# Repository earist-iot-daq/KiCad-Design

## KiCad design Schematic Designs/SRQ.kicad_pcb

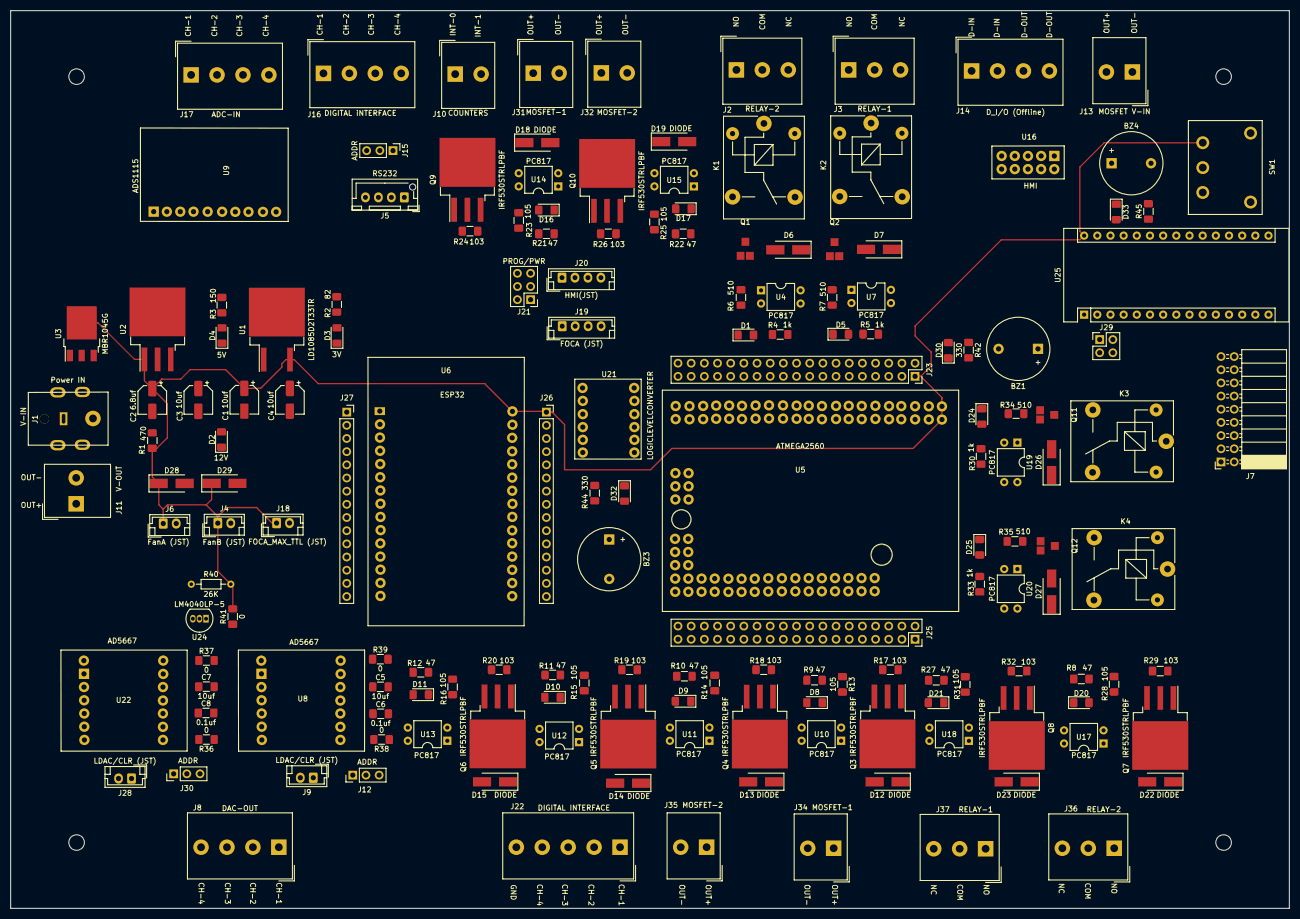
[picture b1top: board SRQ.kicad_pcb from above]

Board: 2 copper layers, 246.6 x 173.1 mm, 163 parts (0 on the bottom side), 240 nets.

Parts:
BZ1, BZ3, BZ4: Buzzer; Buzzer_12x9.5RM7.6
C1, C3, C4: 10uf; CP_Elec_5x5.4
C2: 6.8uf; CP_Elec_5x5.8
C5, C7: 10uf; C_1206_3216Metric_Pad1.42x1.75mm_HandSolder
C6, C8: 0.1uf; C_1206_3216Metric_Pad1.42x1.75mm_HandSolder
D1, D5, D8, D9, D10, D11, D16, D17, D20, D21, D24, D25: LED; LED_1206_3216Metric_Pad1.42x1.75mm_HandSolder
D2, D3, D4, D30, D32, D33: LED; D_1206_3216Metric_Pad1.42x1.75mm_HandSolder
D6, D7, D12, D13, D14, D15, D18, D19, D22, D23, D26, D27, D28, D29: DIODE; D_SMA_Handsoldering
J1: V-IN; DC Power Receptable Jack 8A 2mm Through hole
J2, J36: RELAY-2; Altech_AK300_1x03_P5.00mm_45-Degree
J3, J37: RELAY-1; Altech_AK300_1x03_P5.00mm_45-Degree
J4: FanB (JST); JST_EH_B2B-EH-A_1x02_P2.50mm_Vertical
J5: RS232; JST_XH_B4B-XH-AM_1x04_P2.50mm_Vertical
J6: FanA (JST); JST_EH_B2B-EH-A_1x02_P2.50mm_Vertical
J7: ARDUINO_NANO_pinheaders; PinSocket_2x09_P2.54mm_Horizontal
J8: DAC-OUT; Altech_AK300_1x04_P5.00mm_45-Degree
J9, J28: LDAC/CLR (JST); JST_EH_B2B-EH-A_1x02_P2.50mm_Vertical
J10: COUNTERS; Altech_AK300_1x02_P5.00mm_45-Degree
J11: V-OUT; Altech_AK300_1x02_P5.00mm_45-Degree
J12, J15, J30: ADDR; PinHeader_1x03_P2.54mm_Vertical
J13: MOSFET V-IN; Altech_AK300_1x02_P5.00mm_45-Degree
J14: D_I/O (Offline); Altech_AK300_1x04_P5.00mm_45-Degree
J16: DIGITAL iNTERFACE; Altech_AK300_1x04_P5.00mm_45-Degree
J17: ADC-IN; Altech_AK300_1x04_P5.00mm_45-Degree
J18: FOCA_MAX_TTL (JST); JST_EH_B2B-EH-A_1x02_P2.50mm_Vertical
J19: FOCA (JST); JST_EH_B4B-EH-A_1x04_P2.50mm_Vertical
J20: HMI(JST); JST_EH_B4B-EH-A_1x04_P2.50mm_Vertical
J21: PROG/PWR; PinHeader_2x03_P2.54mm_Vertical
J22: DIGITAL INTERFACE; Altech_AK300_1x05_P5.00mm_45-Degree
J23: ATMEGA_pinheaders; PinSocket_2x19_P2.54mm_Vertical
J25: ATMEGA2560_pinheaders; PinSocket_2x19_P2.54mm_Vertical
J26: ESP32_LEFTpinheaders; PinSocket_1x15_P2.54mm_Vertical
J27: ESP32_RIGHtpinheaders; PinSocket_1x15_P2.54mm_Vertical
J29: PROG; PinHeader_2x02_P2.54mm_Vertical
J31, J34: MOSFET-1; Altech_AK300_1x02_P5.00mm_45-Degree
J32, J35: MOSFET-2; Altech_AK300_1x02_P5.00mm_45-Degree
K1, K2, K3, K4: SANYOU_SRD_Form_C; Relay_SPDT_SANYOU_SRD_Series_Form_C
Q1, Q2, Q11, Q12: TRANSISTOR_NPN; MMBT2222L
Q3, Q4, Q5, Q6, Q7, Q8, Q9, Q10: IRF530STRLPBF; TO-263-3_TabPin2
R1: 470; R_1206_3216Metric_Pad1.42x1.75mm_HandSolder
R2: 82; R_1206_3216Metric_Pad1.42x1.75mm_HandSolder
R3: 150; R_1206_3216Metric_Pad1.42x1.75mm_HandSolder
R4, R5, R30, R33: 1k; R_1206_3216Metric_Pad1.42x1.75mm_HandSolder
R6, R7, R34, R35: 510; R_1206_3216Metric_Pad1.42x1.75mm_HandSolder
R8, R9, R10, R11, R12, R21, R22, R27: 47; R_1206_3216Metric_Pad1.42x1.75mm_HandSolder
R13, R14, R15, R16, R23, R25, R28, R31: 105; R_1206_3216Metric_Pad1.42x1.75mm_HandSolder
R17, R18, R19, R20, R24, R26, R29, R32: 103; R_1206_3216Metric_Pad1.42x1.75mm_HandSolder
R36, R37, R38, R39, R41: 0; R_1206_3216Metric_Pad1.42x1.75mm_HandSolder
R40: 26K; R_Axial_DIN0204_L3.6mm_D1.6mm_P7.62mm_Horizontal
R42, R44, R45: 330; R_1206_3216Metric_Pad1.42x1.75mm_HandSolder
SW1: SW_SPDT; SPDT_5A_120V_On-On_DIP_Toggle_Switch
U1: LD1085D2T33TR; TO-263-2
U2: SPX29300; TO-263-3_TabPin2
U3: MBR1045G; TO-252-3_TabPin4
U4, U7, U10, U11, U12, U13, U14, U15, U17, U18, U19, U20: PC817; DIP-4_W7.62mm
U5: ATMEGA2560; ATMega2560
U6: ESP32; ESP32S_EH
U8, U22: AD5667
U9: ADS1115
U16: HMI; HMI_eh
U21: LOGICLEVELCONVERTER; Logic_LC
U24: LM4040LP-5; TO-92_Inline
U25: ArduinoNANO; Arduino_Nano

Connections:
3.3V: C4.1, R2.1, U1.2, U21.3
5V: C3.1, C5.1, C6.1, C7.1, C8.1, D26.1, D27.1, J5.4, J12.3, J15.3, J30.3, K3.5, K4.5, R3.1, R30.2, R33.2, R36.2, R37.1, R38.2, R39.1, U2.3, U8.9, U9.1, U19.4, U20.4, U21.10, U22.9
12V: C1.1, C2.1, D28.1, D29.1, J4.1, J6.1, J18.1, J23.1, J26.1, R1.1, R40.2, R41.2, SW1.3, U1.3, U2.1, U3.4, U5.1, U6.16, U25.30
A0: J7.17, U25.19
A1: J7.16, U25.20
A2: J7.15, U25.21
A3: J7.14, U25.22
A4: J7.13, U25.23
A5: J7.12, U25.24
A6: J7.11, U25.25
A7: J7.10, U25.26
ALRT: J25.17, U5.55, U9.6
ATMEGA_3V3: J23.4, U5.4
ATMEGA_5V: J23.3, U5.3
ATMEGA_A0: J25.1, U5.39
ATMEGA_A1: J25.2, U5.40
ATMEGA_A2: J25.3, U5.41
ATMEGA_A3: J25.4, U5.42
ATMEGA_A4: J25.5, U5.43
ATMEGA_A5: J25.6, U5.44
ATMEGA_A6: J25.7, U5.45
ATMEGA_A7: J25.8, U5.46
ATMEGA_A8: J25.9, U5.47
ATMEGA_A9: J25.10, U5.48
ATMEGA_A10: J25.11, U5.49
ATMEGA_A11: J25.12, U5.50
ATMEGA_A12: J25.13, U5.51
ATMEGA_A13: J25.14, U5.52
ATMEGA_A14: J25.15, U5.53
ATMEGA_A15: J25.16, U5.54
ATMEGA_AREF: J23.5, U5.5
ATMEGA_D2: J10.2, J23.9, U5.9
ATMEGA_D3: J10.1, J23.10, U5.10
ATMEGA_D4: J23.11, U5.11
ATMEGA_D9: J23.16, U5.16
ATMEGA_D12: J23.19, R42.2, U5.19
ATMEGA_D13: BZ1.1, J23.20, U5.20
ATMEGA_D22: J23.29, U5.29
ATMEGA_D23: J23.30, U5.30
ATMEGA_D24: J23.31, U5.31
ATMEGA_D25: J23.32, U5.32
ATMEGA_D26: J16.4, J23.33, U5.33
ATMEGA_D27: J16.3, J23.34, U5.34
ATMEGA_D28: J16.2, J23.35, U5.35
ATMEGA_D29: J16.1, J23.36, U5.36
ATMEGA_D33: J25.18, U5.56
ATMEGA_D34: J25.19, U5.57
ATMEGA_D35: J25.20, U5.58
ATMEGA_D36: J25.21, U5.59
ATMEGA_D37: J25.22, U5.60
ATMEGA_D38: J25.23, U5.61
ATMEGA_D39: J25.24, U5.62
ATMEGA_D40: J25.25, U5.63
ATMEGA_D41: J25.26, U5.64
ATMEGA_D42: J25.27, U5.65
ATMEGA_D43: J25.28, U5.66
ATMEGA_D44: J25.29, U5.67
ATMEGA_D45: J25.30, U5.68
ATMEGA_D46: J25.31, U5.69
ATMEGA_D47: J25.32, U5.70
ATMEGA_D48: J25.33, U5.71
ATMEGA_D49: J25.34, U5.72
ATMEGA_D50: J25.35, U5.73
ATMEGA_D51: J25.36, U5.74
ATMEGA_D52: J25.37, U5.75
ATMEGA_D53: J25.38, U5.76
ATMEGA_GND: BZ3.2, BZ4.2, C1.2, C2.2, C3.2, C4.2, C5.2, C6.2, C7.2, C8.2, D2.1, D3.1, D4.1, D12.2, D13.2, D14.2, D15.2, D18.2, D19.2, D22.2, D23.2, D28.2, D29.2, D32.1, D33.1, J1.2, J1.3, J4.2, J5.1, J6.2, J11.2, J12.1, J13.2, J15.1, J18.2, J19.4, J20.4, J22.5, J23.2, J26.2, J27.2, J30.1, J31.2, J32.2, J34.2, J35.2, Q1.E, Q2.E, Q11.E, Q12.E, U1.1, U2.2, U5.2, U6.2, U6.17, U8.3, U9.2, U10.2, U10.3, U11.2, U11.3, U12.2, U12.3, U13.2, U13.3, U14.2, U14.3, U15.2, U15.3, U16.5, U17.2, U17.3, U18.2, U18.3, U21.4, U21.9, U22.3, U24.3, U25.29
ATMEGA_RST: J23.6, U5.6
D2: J7.1, U25.5
D3: J7.2, U25.6
D4: J7.3, U25.7
D5: J7.4, U25.8
D6: J7.5, U25.9
D7: J7.6, U25.10
D8: J7.7, U25.11
D9: J7.8, U25.12
D10: J7.9, U25.13
D11: J7.18, U25.14
DOut1: D25.1, J23.37, U5.37
DOut2: D24.1, J23.38, U5.38
ESP_3V3: J27.1, U6.1
ESP_D2: J27.4, U6.4
ESP_D4: J27.5, U6.5
ESP_D5: J27.8, U6.8
ESP_D12: J26.4, R44.2, U6.19
ESP_D13: BZ3.1, J26.3, U6.18
ESP_D14: J26.5, U6.20
ESP_D15: J27.3, U6.3
ESP_D18: J27.9, U6.9
ESP_D19: J27.10, U6.10
ESP_D21: J27.11, U6.11
ESP_D22: J27.14, U6.14
ESP_D23: J27.15, U6.15
ESP_D25: J26.8, U6.23
ESP_D26: J26.7, U6.22
ESP_D27: J26.6, U6.21
ESP_D32: J26.10, U6.25
ESP_D33: J26.9, U6.24
ESP_D34: J26.12, U6.27
ESP_D35: J26.11, U6.26
ESP_EN: J26.15, U6.30
ESP_RX0: J27.12, U6.12
ESP_RX2: J27.6, U6.6, U21.2
ESP_TX0: J27.13, U6.13
ESP_TX2: J27.7, U6.7, U21.1
ESP_VN: J26.13, U6.28
ESP_VP: J26.14, U6.29
IO_4: D5.1, U16.8
IO_5: D1.1, U16.3
IO_6: R21.1, U16.7
IO_7: R22.1, U16.4
unnamed: BZ1.2, D30.1
unnamed: BZ4.1, U25.16
unnamed: D1.2, U4.2
unnamed: D2.2, R1.2
unnamed: D3.2, R2.2
unnamed: D4.2, R3.2
unnamed: D5.2, U7.2
unnamed: D6.1, K1.5, R4.2, U4.4
unnamed: D6.2, K1.2, Q1.C
unnamed: D7.1, K2.5, R5.2, U7.4
unnamed: D7.2, K2.2, Q2.C
unnamed: D8.1, U10.1
unnamed: D8.2, R9.2
unnamed: D9.1, U11.1
unnamed: D9.2, R10.2
unnamed: D10.1, U12.1
unnamed: D10.2, R11.2
unnamed: D11.1, U13.1
unnamed: D11.2, R12.2
unnamed: D12.1, J22.1, Q3.2
unnamed: D13.1, J22.2, Q4.2
unnamed: D14.1, J22.3, Q5.2
unnamed: D15.1, J22.4, Q6.2
unnamed: D16.1, U14.1
unnamed: D16.2, R21.2
unnamed: D17.1, U15.1
unnamed: D17.2, R22.2
unnamed: D18.1, J31.1, Q9.2
unnamed: D19.1, J32.1, Q10.2
unnamed: D20.1, U17.1
unnamed: D20.2, R8.2
unnamed: D21.1, U18.1
unnamed: D21.2, R27.2
unnamed: D22.1, J34.1, Q7.2
unnamed: D23.1, J35.1, Q8.2
unnamed: D24.2, U19.2
unnamed: D25.2, U20.2
unnamed: D26.2, K3.2, Q11.C
unnamed: D27.2, K4.2, Q12.C
unnamed: D30.2, R42.1
unnamed: D32.2, R44.1
unnamed: D33.2, R45.1
unnamed: J1.4, J11.1, U3.1, U3.3
unnamed: J2.1, K1.3
unnamed: J2.2, K1.1
unnamed: J2.3, K1.4
unnamed: J3.1, K2.3
unnamed: J3.2, K2.1
unnamed: J3.3, K2.4
unnamed: J8.1, U8.1
unnamed: J8.2, U8.2
unnamed: J8.3, U22.1
unnamed: J8.4, U22.2
unnamed: J9.1, U8.4
unnamed: J9.2, U8.5
unnamed: J12.2, U8.6
unnamed: J13.1, SW1.1
unnamed: J14.1, U16.10
unnamed: J14.2, U16.1
unnamed: J14.3, U16.9
unnamed: J14.4, U16.2
unnamed: J15.2, U9.5
unnamed: J17.1, U9.7
unnamed: J17.2, U9.8
unnamed: J17.3, U9.9
unnamed: J17.4, U9.10
unnamed: J19.1, J20.1
unnamed: J19.2, J21.1
unnamed: J19.3, J21.6
unnamed: J20.2, J21.3
unnamed: J20.3, J21.4
unnamed: J28.1, U22.4
unnamed: J28.2, U22.5
unnamed: J29.2, U25.2
unnamed: J29.4, U25.1
unnamed: J30.2, U22.6
unnamed: J36.1, K3.3
unnamed: J36.2, K3.1
unnamed: J36.3, K3.4
unnamed: J37.1, K4.3
unnamed: J37.2, K4.1
unnamed: J37.3, K4.4
unnamed: Q1.B, R6.2
unnamed: Q2.B, R7.2
unnamed: Q3.1, R17.1
unnamed: Q4.1, R18.1
unnamed: Q5.1, R19.1
unnamed: Q6.1, R20.1
unnamed: Q7.1, R29.1
unnamed: Q8.1, R32.1
unnamed: Q9.1, R24.1
unnamed: Q10.1, R26.1
unnamed: Q11.B, R34.2
unnamed: Q12.B, R35.2
unnamed: R4.1, U4.1
unnamed: R5.1, U7.1
unnamed: R6.1, U4.3
unnamed: R7.1, U7.3
unnamed: R13.1, R17.2, U10.4
unnamed: R14.1, R18.2, U11.4
unnamed: R15.1, R19.2, U12.4
unnamed: R16.1, R20.2, U13.4
unnamed: R23.1, R24.2, U14.4
unnamed: R25.1, R26.2, U15.4
unnamed: R28.1, R29.2, U17.4
unnamed: R30.1, U19.1
unnamed: R31.1, R32.2, U18.4
unnamed: R33.1, U20.1
unnamed: R34.1, U19.3
unnamed: R35.1, U20.3
unnamed: R40.1, R41.1, U8.10, U22.10, U24.2
unnamed: R45.2, U25.15
PWM1: J23.12, R9.1, U5.12
PWM2: J23.13, R10.1, U5.13
PWM3: J23.14, R11.1, U5.14
PWM4: J23.15, R12.1, U5.15
PWM5: J23.17, R8.1, U5.17
PWM6: J23.18, R27.1, U5.18
RX0: J23.7, J29.3, U5.7
RX1: J21.5, J23.25, U5.25
RX2: J23.23, U5.23, U21.11
RX3: J5.2, J23.21, U5.21
SCL: J23.28, R36.1, R38.1, U5.28, U8.7, U9.3, U22.7
SDA: J23.27, R37.2, R39.2, U5.27, U8.8, U9.4, U22.8
SWITCH: Q3.3, Q4.3, Q5.3, Q6.3, Q7.3, Q8.3, Q9.3, Q10.3, R13.2, R14.2, R15.2, R16.2, R23.2, R25.2, R28.2, R31.2, SW1.2
TX0: J23.8, J29.1, U5.8
TX1: J21.2, J23.26, U5.26
TX2: J23.24, U5.24, U21.12
TX3: J5.3, J23.22, U5.22

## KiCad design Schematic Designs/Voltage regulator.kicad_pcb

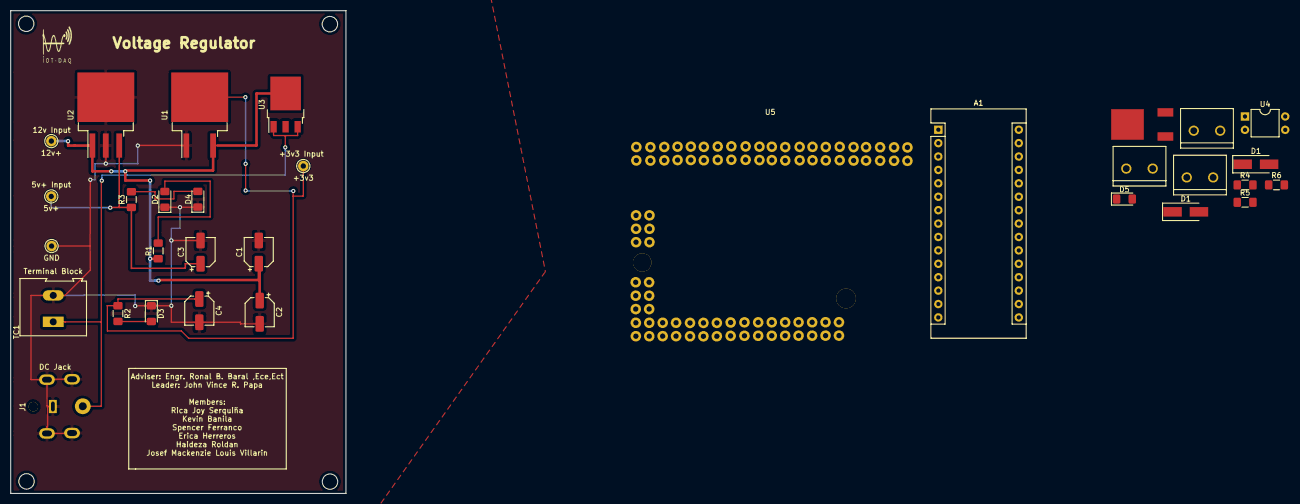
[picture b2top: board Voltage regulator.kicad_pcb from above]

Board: 2 copper layers, 63.5 x 91.4 mm, 32 parts (0 on the bottom side), 17 nets.

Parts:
5v+, 12v+: Pin_D1.0mm_L10.0mm
+3v3: Pin_D1.0mm_L10.0mm
A1: Arduino_Nano_v3.x; Arduino_Nano
C1, C3, C4: 10uf; CP_Elec_5x5.4
C2: 6.8uf; CP_Elec_5x5.8
D1, D1#2: DIODE; D_SMA_Handsoldering
D2, D3, D4: LED; D_1206_3216Metric_Pad1.42x1.75mm_HandSolder
D5: LED; LED_1206_3216Metric_Pad1.42x1.75mm_HandSolder
GND: Pin_D1.0mm_L10.0mm
J1: dc-042c-x-2.5_DC-042C-X-2.5; DC Power Receptable Jack 8A 2mm Through hole
J2, J3, J4: Screw_Terminal_01x02; SCREWTERMINAL-5MM-2
Q1: MOSFET_P; DPAK_FET
R1: 470; R_1206_3216Metric_Pad1.42x1.75mm_HandSolder
R2: 82; R_1206_3216Metric_Pad1.42x1.75mm_HandSolder
R3: 150; R_1206_3216Metric_Pad1.42x1.75mm_HandSolder
R4: 47; R_1206_3216Metric_Pad1.42x1.75mm_HandSolder
R5: 105; R_1206_3216Metric_Pad1.42x1.75mm_HandSolder
R6: 103; R_1206_3216Metric_Pad1.42x1.75mm_HandSolder
TC1: Thermocouple_Block; TerminalBlock_Altech_AK300-2_P5.00mm
U1: LD1085D2T33TR; TO-263-2
U2: SPX29300T-L-5; TO-263-3_TabPin2
U3: MBR1045G; TO-252-3_TabPin4
U4: PC817; DIP-4_W7.62mm
U5: ATMEGA2562; ATMega2560

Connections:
3.3V: C4.1, R2.1, U1.2
5V: C3.1, R3.1, U2.3
12V: C1.1, C2.1, R1.1, U1.3, U2.1, U3.4
GND: C1.2, C2.2, C3.2, C4.2, D2.1, D3.1, D4.1, GND.1, J1.2, J1.3, TC1.2, U1.1, U2.2
unnamed: D1.1, J4.1, Q1.D
unnamed: D1.2, J3.2, J4.2, U4.3
unnamed: D2.2, R1.2
unnamed: D3.2, R2.2
unnamed: D4.2, R3.2
unnamed: D5.1, U4.1
unnamed: D5.2, R4.2
unnamed: J1.4, TC1.1, U3.1, U3.3
unnamed: J2.1, U4.2
unnamed: J2.2, R4.1
unnamed: J3.1, Q1.S, R5.2
unnamed: Q1.G, R6.1
unnamed: R5.1, R6.2, U4.4

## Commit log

2021-03-12 Create Schematic Design REV1
